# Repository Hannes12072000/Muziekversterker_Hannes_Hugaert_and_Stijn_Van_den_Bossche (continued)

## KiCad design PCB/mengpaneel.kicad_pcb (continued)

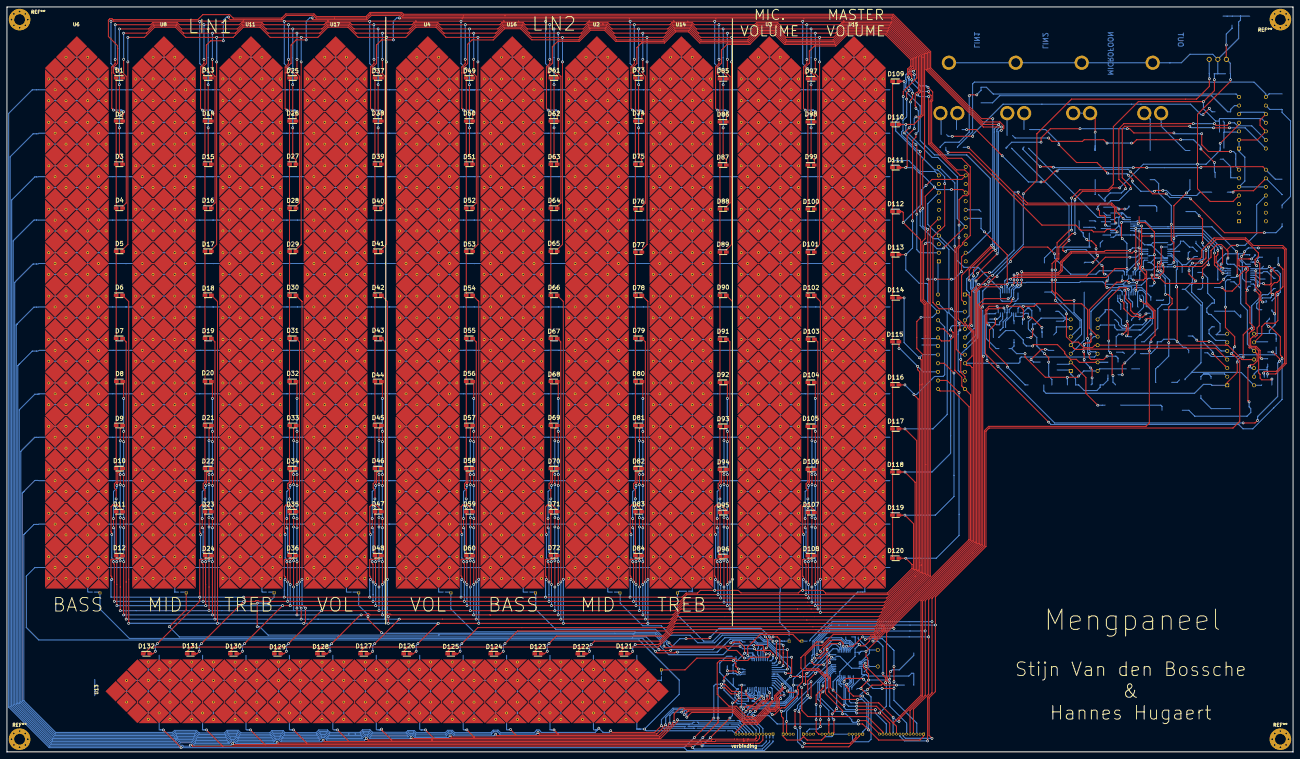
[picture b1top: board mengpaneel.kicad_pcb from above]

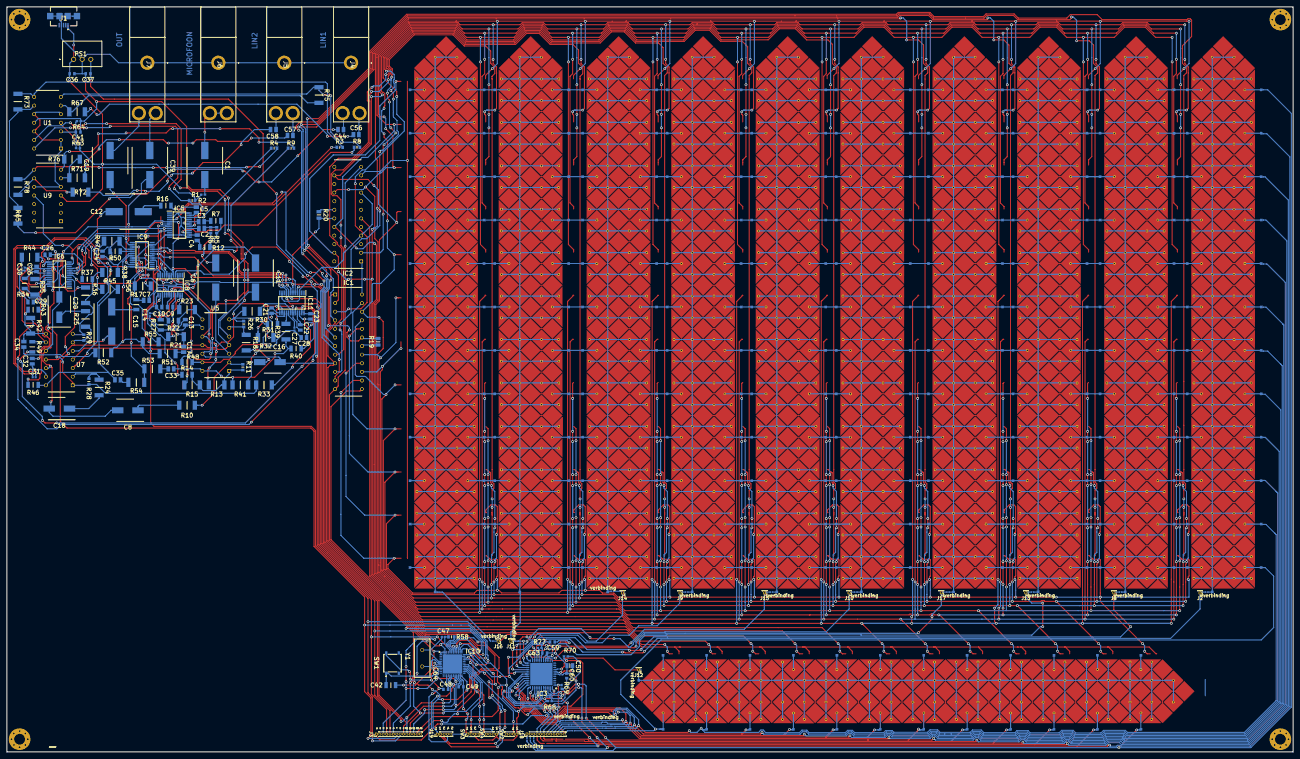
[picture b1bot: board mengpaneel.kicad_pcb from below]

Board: 2 copper layers, 380.2 x 220.2 mm, 320 parts (176 on the bottom side), 300 nets.

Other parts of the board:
.: Fuse_0201_0603Metric
verbinding: Fuse_0201_0603Metric
verbinding#2, verbinding#3, verbinding#4, verbinding#5, verbinding#6, verbinding#7, verbinding#8, verbinding#9, verbinding#10, verbinding#11, verbinding#12, verbinding#13, verbinding#14, verbinding#15: Fuse_0201_0603Metric

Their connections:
laag_5: verbinding.1, verbinding.2; also elsewhere on the board
laag_6: verbinding#2.1, verbinding#2.2; also elsewhere on the board
laag_9: verbinding#3.1, verbinding#3.2; also elsewhere on the board
laag_10: ..1, ..2; also elsewhere on the board
laag_11: verbinding#4.1, verbinding#4.2; also elsewhere on the board
slider_1: verbinding#15.1, verbinding#15.2; also elsewhere on the board
slider_2: verbinding#14.1, verbinding#14.2; also elsewhere on the board
slider_3: verbinding#11.1, verbinding#11.2; also elsewhere on the board
slider_4: verbinding#9.1, verbinding#9.2; also elsewhere on the board
slider_5: verbinding#7.1, verbinding#7.2; also elsewhere on the board
slider_6: verbinding#13.1, verbinding#13.2; also elsewhere on the board
slider_7: verbinding#5.1, verbinding#5.2; also elsewhere on the board
slider_8: verbinding#10.1, verbinding#10.2; also elsewhere on the board
slider_9: verbinding#8.1, verbinding#8.2; also elsewhere on the board
slider_10: verbinding#6.1, verbinding#6.2; also elsewhere on the board
slider_11: verbinding#12.1, verbinding#12.2; also elsewhere on the board

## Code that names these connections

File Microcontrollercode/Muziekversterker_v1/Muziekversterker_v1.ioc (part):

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Mcu.Name=STM32F411C(C-E)Ux
Mcu.Package=UFQFPN48
Mcu.UserName=STM32F411CEUx
PA12.GPIOParameters=GPIO_Label
PA12.GPIO_Label=CS_POT5
PA12.Signal=GPIO_Output
PA13.Mode=Serial_Wire
PA13.Signal=SYS_JTMS-SWDIO
PA14.Mode=Serial_Wire
PA14.Signal=SYS_JTCK-SWCLK
PA15.GPIOParameters=GPIO_Label
PA15.GPIO_Label=CS_POT4
PA15.Signal=GPIO_Output
PA2.GPIOParameters=GPIO_Label
PA2.GPIO_Label=touch_reset
PA2.Signal=GPIO_Output
PA5.Mode=TX_Only_Simplex_Unidirect_Master
PA5.Signal=SPI1_SCK
PA7.Mode=TX_Only_Simplex_Unidirect_Master
PA7.Signal=SPI1_MOSI
PB0.GPIOParameters=GPIO_ModeDefaultEXTI
PB0.GPIO_ModeDefaultEXTI=GPIO_MODE_IT_RISING
PB0.Signal=GPXTI0
PB1.GPIOParameters=GPIO_Label
PB1.GPIO_Label=SD_Step_Up
PB1.Signal=GPIO_Output
PB10.Mode=TX_Only_Simplex_Unidirect_Master
PB10.Signal=SPI2_SCK
PB12.Signal=GPIO_Output
PB15.Mode=TX_Only_Simplex_Unidirect_Master
PB15.Signal=SPI2_MOSI
PB2.GPIOParameters=GPIO_Label
PB2.GPIO_Label=CS_LEDS
PB2.Signal=GPIO_Output
PB3.GPIOParameters=GPIO_Label
PB3.GPIO_Label=CS_POT3
PB3.Signal=GPIO_Output
PB4.GPIOParameters=GPIO_Label
PB4.GPIO_Label=CS_POT2
PB4.Signal=GPIO_Output
PB5.GPIOParameters=GPIO_Label
PB5.GPIO_Label=CS_POT1
PB5.Signal=GPIO_Output
PB6.Mode=I2C
PB6.Signal=I2C1_SCL
PB7.Mode=I2C
PB7.Signal=I2C1_SDA
PH0\ -\ OSC_IN.Mode=HSE-External-Oscillator
PH0\ -\ OSC_IN.Signal=RCC_OSC_IN
PH1\ -\ OSC_OUT.Mode=HSE-External-Oscillator
PH1\ -\ OSC_OUT.Signal=RCC_OSC_OUT
RCC.HSE_VALUE=8000000
RCC.SYSCLKFreq_VALUE=48000000
RCC.SYSCLKSource=RCC_SYSCLKSOURCE_PLLCLK
board=custom

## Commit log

2021-03-08 Create test
2021-03-08 Create placeholder
2021-03-16 Footprints sliders aangepast + slider links-rechts footprint toegevoegd
2021-03-23 update 23/03/2021 alle libraries aangepast naar definitieve componenten
2021-03-23 Added mengpaneel footprint & schema's voor de tweede keer
2021-03-23 added LR_footprint manually
2021-03-23 associatie footprint associatie footprint
2021-03-23 Startcode toegevoegd (automatisch gegenereerd door CubeMX) + Paar touchpad footprints toegevoegd (hopelijk geen problemen hiervan)
2021-03-23 Startcode toegevoegd, autogenerated door CubeMX
2021-03-23 Start van State diagram added
2021-03-23 23/03/2021 verdere aanpassing
2021-03-27 tussentijdse vernieuwing 27/03/2021
2021-04-02 PCB bijna af
2021-04-04 Ho ho ho vrolijke Pasen iedereen.🐇🧺🥚 pcb bijna af
2021-04-05 PCB af alleen nog wachten op touchsliders
2021-04-07 PCB af nu wachten op de docenten hun feedback.
2021-04-08 created PDF versions of KICad schema & PCB, version of 08/04, 16:30
2021-04-08 edited PCB slightly to modify text for Bass - medium - treble
2021-04-15 Kleine foutjes nog aangepast.
2021-04-15 kleine aanpassing aan PCB
2021-04-15 Document beginnen invullen
2021-04-17 PCB doet aan alle normen van de docent
2021-04-18 Document bij getypt.
2021-04-20 word in git steken.
2021-04-20 word eindverslag ingevoegd
2021-04-20 initialisaties SPI functies
2021-04-20 pcb oke
2021-04-27 Software schema verder gewerkt
2021-04-27 added basic SPI & I2C write/read commands
2021-05-04 Extra functionaliteit I2C toegevoegd om op verder te werken
2021-05-04 Word document aangepast
2021-05-07 Led controller code aangevuld, mogelijks probleem met leds aan te sturen, te testen
2021-05-10 Een stuk van het gebruikte componenten een beetje herschreven en spelfouten gecorrigeerd.
2021-05-17 Touchcontroller initialisatie verder afgwerkt, nog enkele zaken aan te passen + veel testen obviously
2021-05-17 enkele kleine bugfixes en aanpassingen
2021-05-17 added leddisplaydriver code
2021-05-17 kleine dingen aangepast + code om touchController te testen
2021-05-18 Conversie toegevoegd om touchwaarden om te zetten naar bruikbare pot-values & ledvalues
2021-05-18 Extra dingen toegevoegd
2021-05-19 Version 3 v microcontrollercode, deze is geschreven voor STM32F746G-DISCO bordje (EMSYS-bordje)
2021-05-21 Zaken van hardware al aangepast en herschreven
2021-05-21 Deel hardware verder herschreven en aangepast
2021-05-21 Software deel toegevoegd
2021-05-21 Finale versie verslag
2021-05-26 laatste versie software voor demo
2021-05-26 enkele kleine aanpassingen in witregels
